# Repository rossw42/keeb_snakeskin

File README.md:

# Keyboard Snakeskin

Automatically generate a 3D printable case and magnetic carrycase for your custom split keyboard PCBs, from just the
outline. Also generates cases for other PCBs.

This case design generally uses a friction fit to get the PCB to stay in the
case. You can use hot glue instead if your printer tolerances are bad or
you want a sturdier/more permanent fit.
Cases have a removal cutout in one part of the wall for you to pull the case out
after pushing it in.

Inspired by and in collaboration with the [Compression keyboard](https://github.com/compressionKeyboards/compression4c) by Bennett Hermanoff. ([More images here](https://compressionkeyboards.com/)).

|  | |
| ------------- | -------------- |
|  *Example case rendered from the [maizeless](https://github.com/BlueDrink9/maizeless) PCB, with honeycomb base.* |  *Example [ferris](https://github.com/pierrechevalier83/ferris) case* |
|  *Corne* |  *Lily58 with a fat honeycomb* |
| *Carrycase with one case inside*. The carrycase is mirrored around the center, to allow for two halves of a split board to be carried together.  | Just the carrycase  |
| With tenting legs and strap loop  | One leg open  |

## Features

* Gives you a protective case for your keyboard PCBs, even if you aren't using
a popular design.
* Compact magnetic carrycase gives you ultimate portability, quick to unclip
and start typing (no faffing with bags or zips).
* Quick-tenting mechanism with quick-unfold leg(s), customisable for multiple angles and heights.
* Optional honeycomb base, to look great, save on weight and plastic, and show
off your custom PCB and top-notch (😉) soldering.
* Loop for strap attachment
    * Attach the boards to your legs for a standing setup,
    * Tie to a chair arm for a more ergonomic sitting setup,
    * use as a handle or tie to your bag.
* Works with both split and non-split board PCBs
* Works with any PCB of unusual shape, even non-keyboard PCBs for whatever random project you want an enclosure for.
* If you don't care about the magnets, you can input an SVG outline of a board with an existing case (e.g. commercial Ergodox or Voyager) and just print a carrycase for protecting the keys.
* Outputs as `STL` or `STEP`, so you can use this as the base shape for your own more exciting custom case designs (as long as they are provided under the same licence).

### Future feature ideas

* Unibody case generator, with customisable distances and angles. Possibly even
a temporary one (sit/clip your regular case into it to make it a unibody board
for the couch, then lift them up and use them separately at your desk).
* Integrate features with the carrycase. Possibly allow clipping the board
edges into the carrycase for a unibody angle, or clip the board onto the top as
a tenting mechanism.
* Strap loop on carrycase as a handle or to attach to a bag.
* Wrist wrest that magnetically snap to the case.
* Folding hinge join between the two halves, similar to the [Leaf fold](https://www.reddit.com/r/ErgoMechKeyboards/comments/1g9hv4a/introducing_leaf_fold_an_ultra_portable_keyboard/)
* Insets/holes under case to sit rubber feet in. (You can still use them currently, but they stick out of the bottom and may not be as stable.) This feature would probably be configured with a list of angles to place the holes at around the case edge (as well as hole diameter and depth, and maybe distance from the case edge). Subtracting holes from the final case would be quite easy to do manually from the .step output, so if you need this feature, you can probably do it yourself.
* Standoffs to screw in PCB --- I'm not likely to do this (at least certainly not automatically generating them from the PCB holes). This would be easy to add yourself from the .step output in another program like freecad, if you really need these.
* Different patterns for the bottom (like the popular organic void patterns).
* Position eyelets for slower but more flexibly screw-based tenting legs (like often seen in nyquist cases).

> See anything you like? Open an issue and express interest

**Tip**: Take note of the version of snakeskin you use to build your cases, as
well as your current config.
You may want to print new parts as features are released, and you'll want the
same config and major version to ensure the case is compatible.
Features may also get added that change case designs, and you'll want to know
that if you want to reprint parts that you already have.

## Usage

Overall:
1. In KiCad, export **just the edge cuts layer** as an SVG.
2. Customise the design parameters for your board, either by creating/modifying a config json, or passing arguments. At minimum I would suggest tweaking the cutout and magnet positioning for your board, although I suggest verifying the program runs without errors on your SVG with defaults before tweaking too many parameters.
3. Run `snakeskin.py --config path/to/config.json path/to/edge_cuts.svg`.
4. (Optional) Read the [Configuration](#configuration) section to tweak for your board.

Note: this is still a young project, so please feel free to open issues. Include the SVG and config you are having issues with.

### Install

`pip install --user keeb-snakeskin` installs this package and dependencies, and
should create a new executable `snakeskin` in your python scripts folder.

Use `pip install --user git+https://github.com/BlueDrink9/keeb_snakeskin.git` for the latest git version.

#### Windows Installation

If you're on Windows with Python 3.14+, you may encounter compatibility issues since `build123d` and its dependencies don't yet support the latest Python versions. Here's how to resolve it:

1. **Use Python 3.13** (recommended):
   ```powershell
   # Check available Python versions
   py -0
   
   # Install with Python 3.13
   py -3.13 -m pip install --user keeb-snakeskin
   ```

2. **Run snakeskin with Python 3.13**:
   ```powershell
   py -3.13 -m keeb_snakeskin.snakeskin --output_dir my_case path/to/edge_cuts.svg
   ```

If you're installing from source on Windows:
```powershell
# Clone the repository
git clone https://github.com/BlueDrink9/keeb_snakeskin.git
cd keeb_snakeskin

# Install in development mode with Python 3.13
py -3.13 -m pip install -e .

# Run with Python 3.13
py -3.13 -m keeb_snakeskin.snakeskin --output_dir my_case preset_outlines/ferris.svg
```

### Input File

The program requires an SVG outline of the PCB, which is then used as the base shape for the case.
You can pass in either a:
* `.svg` file
* `kicad_pcb` file (if `kicad-cli` is installed and on your `$PATH`)

If KiCad cannot be found, you will have to convert your file to svg manually.

Example usage:
```bash
snakeskin -o maizeless ~/src/maizeless/pcb/build/maizeless.svg --split false
```

The `-o` option specifies the output directory for your case files. If it is
not an absolute path, it will be created as a subfolder or file within the
`build` folder.

In this case the output would be `./build/maizeless/case.step` and `./build/maizeless/case_mirrored.stl`

`--split false` sets a configuration option. See the [Configuration](#configuration) section for more information on how to customise the case design.

#### Getting the starting svg

Clean and working outline svgs for some boards are already included in the `./preset_outlines/` folder.
Currently this includes:
* [ferris (0.1)](https://github.com/pierrechevalier83/ferris)
* [maizeless](https://github.com/BlueDrink9/maizeless)
* [corne](https://github.com/foostan/crkbd) (cherry version, not sure what compatibility is like with other versions - it depends purely on the PCB outline)
* [Sofle](https://github.com/josefadamcik/SofleKeyboard) (v1 --- v2 works directly from the `.kicad_pcb`)

In kicad, export just the edge.cuts layer as plot format `svg` (board only, not page).
Note that KiCad has two ways to do this - plotting fabrication as an SVG, and exporting just edge as an SVG directly. The latter gives a more stable output.
Ensure coordinate output is mm if relevant, and all the 'plot' general options are unchecked.

You can do this with the cli via
`kicad-cli pcb export svg  --exclude-drawing-sheet --drill-shape-opt 1 --layers Edge.Cuts --output build/outline.svg ~/src/maizeless/pcb/maizeless.kicad_pcb`.
If you have kicad-cli on your `$PATH`, you can directly pass the `.kicad_pcb`
file to `snakeskin.py` and this export will be done for you.

If you only have a [keyboard-layout-editor](https://keyboard-layout-editor.com/) file, you can
generate an input SVG or KiCad PCB first with tools like
* https://github.com/fcoury/kbpcb
* https://kb.xyz.is/
* https://github.com/adamws/keyboard-tools

#### Troublesome PCBs/input files

This program requires the PCB outline to be a single, closed path. Complicated
PCBs will not work out of the box, for example ones with:

* large irregular holes (e.g. LED holes; vias and holes for keyboard switches are fine)
* internal cutouts (like for mid-mount connectors),
* breakable/mouse nibble columns,
* multiple halves
* multiple halves in a PCB frame

That being said, you can still use this program; you'll just need to manually
edit the SVG outline. Usually this will be as simple as removing the second
half or any internal holes. If you do this for a popular board, please open a PR to
share the resulting SVG (and ideally config json) in `./preset_outlines/`

**Note**: SVG outlines must not contain borders or technical drawings, as are
often exported by default in KiCad. Remove these if you are using an SVG input.

##### Troubleshooting steps to try
* First check with default settings
* Remove any internal holes or cutouts from the SVG
* Set `tiny_edge_rounding` to `True` in your config
* In Inkscape, select the outline, then `Path -> Stroke to Path`, then `Path -> Union`
* In Inkscape, select the outline, then `Path -> Simplify`
* In Inkscape, edit path nodes and ensure they are all connected (small
disconnections should be handled by the code, but large ones, especially in PCBs with bezier edges, may cause issues). To connect them, go to node edit mode, and draw a box around each node and each close pairs of nodes (drawing a box is important, don't just click) to select them both, then double-click `Join selected nodes` in the node editing toolbar.
* Note that KiCad usually exports a double layer for the edge cuts, so you may
  need to delete one before simplifying.

#### Other PCB file formats
##### DXF

These are easily converted to SVG in Inkscape or other tools, so Snakeskin doesn't support them directly.
The inkscape command line will not export them correctly; the GUI must be used.
Open the DXF, then save as an SVG. Do not export as SVG, this may change the
shape.

##### Gerber

Only use this format if you can't get an outline some other way. The steps below should be unnecessary if you can get an SVG or KiCad PCB.

Edge cut exports in gerber format (i.e. `.gm1` or `.gbr`) don't output an
outline, rather they output a thin shape surrounding the board that *looks*
like an outline. You will need to modify this, e.g. in Inkscape, to get a
single outline path. For convenience, passing the `.gm1` file to `snakeskin`
will output an SVG of the edge cuts in the build folder, which you can then
modify and pass back in. (Requires the `pygerber` pip package to be installed.)

To fix this in Inkscape, you can:
1. Select all, then Path -> Stroke to Path (ctrl + alt + c)
2. Edit -> Find and replace to search and select all paths with "circle" in their id, then delete them.
3. Go to preferences (Edit -> Preferences -> imported images) and set the "Resolution for create bitmap copy" to 1000 dpi.
4. Select the paths, then Edit -> Make a bitmap copy.
5. Select the bitmap copy, go to Path -> Trace bitmap, select detection mode to "centerline tracing (autotrace)".
6. Ensure the path is closed (if there are gaps, you can use the node editing tool to connect the ends of the path).
7. Compare the result against the original paths, and tweak nodes to get it as close as possible.
8. Delete any other paths and objects under the view -> layers and objects panel, to ensure only the outline is left.

### Printing

Designed for PLA, but I've had suggestions that TPU will create a great softer,
more skinlike case. If you have access to it, I would suggest trying that - at
least for the inner case, if not the legs and carrycase.

#### Supports
These designs are designed to be printed in PLA without supports where possible. There
is only two severe (90 degree) overhang in the design, which is the first
blocker of the carrycase and the first carrycase finger cutout.
These should be the only parts that needs supports with the default featureset.
Setting your printer to only print overhangs over 70 degrees should be enough
to automatically support only these parts.

If you aren't printing the carrycase, you shouldn't need supports at all.
If you are using advanced features like the strap loop, you may need additional supports.
If `flush_carrycase_lip` is `False`, you will need short supports all around the bottom of the
carrycase, and its top lip. Again, setting overhangs to 70 degrees should
allocate supports appropriately.

### Assembly

For the basic case, just insert the PCB with a bit of force to get the friction
fit. You may choose to add hot clue underneath for a more permanent fit.

#### Carrycase

The only additional assembly required is inserting magnets. Check out [the Compression
video](https://www.youtube.com/watch?v=eRLCBHWX4eQ&t=905s) to get the general idea.
Only the carrycase magnets should need glue, the case magnets should be held in
by the PCB.

The magnets can be tricky to insert, because you need the orientation lined up between the case and carrycase, and if adjacent magnets are close together, they will interfere with the alignment during placement.
The easiest way to insert the magnets is to do the carrycase first, gluing the magnets that are far away from each other first, letting them dry, then doing the magnet locations adjacent to them.
Then, insert the cases into the carrycase one at a time and insert the magnets, letting the glued carrycase magnets orient the case magnets for you.

#### Tenting legs
1. Align the leg hinges with the case hinges (there should only be one sensible way they fit) and insert the nut.
Screw the bolt in.
2. Add a small piece of velcro to the top of the smallest leg. Add the other
   piece, then press the leg up into the case. Ideally the second piece should then glue to the
PCB. The velcro holds it in place. Feel free to come up with other mechanisms
for keeping it in place, but velcro is an easy solution that doesn't require
much force to remove. I got my velcro from an old bike helmet.

### Visual configurator (browser)

If editing JSON by hand sounds painful, there's a local HTML configurator that
renders your PCB outline and lets you drag the cutout/magnet/lip positions
around the case wall, then download the resulting `config.json`.

It runs entirely in the browser, with no build step or server configuration needed.

#### Launching the Configurator

**Linux/Mac:**
```sh
cd path/to/keeb_snakeskin
make configurator
# or manually:
python -m http.server 8771
```

Then open http://localhost:8771/configurator/ in your browser.

**Windows:**
```powershell
cd path\to\keeb_snakeskin
python -m http.server 8771
```

Then open http://localhost:8771/configurator/ in your browser.

#### Using the Configurator

1. **Load a PCB outline** — Click "Load SVG" and select your edge cuts file, or pick a preset outline
2. **Load a config (optional)** — Click "Load config JSON" to start from an existing config, or pick a preset
3. **Adjust parameters** — Edit the form fields on the right, or drag handles on the canvas:
   - Drag the **cutout handle** to reposition the removal cutout
   - Drag **magnet/lip handles** if using a carrycase
   - Drag **additional cutout handles** for TRRS cables or other features
4. **Download your config** — Click "Download config.json" and enter a name
5. **Generate your case** — Use the downloaded config with snakeskin

#### Generating Cases from Downloaded Config

Once you've downloaded `config.json` from the configurator:

Linux/Mac:
```sh
snakeskin -c config.json -o my-board path/to/edge_cuts.svg
```

Windows with Python 3.13:
```powershell
py -3.13 -m keeb_snakeskin.snakeskin -c config.json --output_dir my-board path/to/edge_cuts.svg
```

The downloaded JSON contains only fields that differ from the defaults, so
upgrading snakeskin won't drag stale values along.

### Configuration

Other than the case design parameters below, you can also input the following
arguments:
- `-o`, `--output`: Output directory or file path (default: "build")
- `-c`, `--config`: Path to the JSON configuration file

The following tables describe the possible variables you can specify for
your case creation.
To modify the paramters, pass a path to a `.json` file with
`-c path/to/cfg.json`, and/or pass individual parameters as command line arguments.
See `python snakeskin.py --help` for more information and for defaults.
The json should have anything you want to override from
defaults specified as a top level key:value. See `./preset_configs/` for
examples.
Using both the json and command line argument for a parameter will take the
command line argument as priority.

You may prefer to modify an existing config, from `./preset_configs/`.
Currently there are configs for:
* [ferris](https://github.com/pierrechevalier83/ferris)
* [maizeless](https://github.com/BlueDrink9/maizeless)
* [corne](https://github.com/foostan/crkbd) (cherry version, although it may not have enough height in the carrycase for cherry keycaps - measure and tweak yourself!)
* [Sofle (v1 and v2)](https://github.com/josefadamcik/SofleKeyboard)
* [Lily58](https://github.com/kata0510/Lily58)

Please note that these configs are on a best-effort basis only, and so far only
the Maizeless has been tested on a real print.

| Parameter name | Example value + unit| Description |
| -------------- | ------------- | ----------- |
| `split`| True | If True, generate mirrored pair of files for a split board |
| `carrycase` | True | Whether the output designs should incorporate the compression-style carrycase. Will affect the main case as well. |
| `honeycomb_base` | True | Make the base of the case a honeycombed/hexagon cage instead of solid |
| `flush_carrycase_lip` | True | Two options for holding the pcb case into the carrycase: a lip that extends into the carrycase center, with a matching cutout in the pcb case; or, a lip that sits a bit above and below the carrycase. If false, the pcb case will have a flat bottom and your tolerances between the case and carrycase can be tighter, giving a better fit when in the case. However, it will require more supports when printing. |
| `strap_loop` | False | Adds a loop on the left most end of the boards for a strap, e.g. for mounting on legs or chair arms. Experimental. If you want something on the other side, also include the tenting flap hinge and use the bolt. |
| `tenting_stand` | False | Use the special quick-deploy tenting mechanism. This parameter adds the hinge to the case (and a gap for it in the carrycase) and exports the requested tenting flaps to the output directory. This creates a hinge at the end of the case, which is designed for a hex nut and countersunk bolt of customisable length. |
| `output_filetype` | `.step` | `.step` or `.stl`. What filetype the case will be exported as. |
| `tiny_edge_rounding` | False | Try enabling this if your case is erroring out with an OCP error, or other invalid shape error. Small hack to work around engine bugs when your outline has tiny edges that may cause problems during offset or extrude operations. May also make things worse, and will very slightly round off internal corners (which shouldn't prevent the PCB from fitting) |
| `simplify_beziers` | False | Try enabling this if your case is erroring out with an OCP error, or other invalid shape error. In some PCB outlines where rounded edges are defined using beziers (e.g. the corne), the 3D engine fails at offsetting or tapering the edges. This option converts beziers to straight line approximations. The approximation is crude, so you may get more accurate results if you do this yourself in inkscape with Extensions > modify path > Approximate curves by straight lines. This setting will probably cut corners a little, making the fit of the case around the PCB a bit tighter. Either increase the tolerance (if you have a lot of corners) or just carve out any tight bits after printing. |
| `base_z_thickness` | 3 mm | Z thickness of bottom of the case, in mm |
| `wall_xy_thickness` | 3 mm | Thickness/width in X and Y of the wall around the edge of the PCB, holding it in the case.  Top and bottom wall tolerance will also affect the thickness that actually gets printed. Recommend 2 + `magnet_separation_distance` if you're using the carrycase, so the magnets don't rattle. If it's larger, you'll have to glue the magnets into the case as well as the carrycase. If you are using the carrycase and have tall keys (i.e. not flat-soldered chocs) close to the edge of the PCB, you may need to make this bigger and tweak the carrycase lip to ensure enough clearance of the carrycase blocker when you insert the board. |
| `wall_z_height` | 4.0 mm | Z height of the wall **from the bottom of the PCB** (total case wall height will include z_space_under_pcb). The default includes room for magnets for the carrycase. If you aren't adding a carrycase, 1.6 is a good height for a standard PCB thickness if you just want to cover the pcb. |
| `z_space_under_pcb` | 1 mm | The size of the gap beneath the PCB, to leave room for through-hole pins, wires, hotswap sockets etc on the underside. Modify this to at least 1.85 if you are using kailh hotswap sockets under the PCB, for example. Also increase it if you want to have bigger tolerences for the fit and need more space for the walls to narrow in. By default, leaves just enough space for the pins of a choc switch directly soldered into a 1.6 mm pcb (which I measure stick out at about 0.83 mm). |
| `wall_xy_bottom_tolerance` | -0.3 mm | Amount of space between the PCB and the case walls near the case bottom, where PCB should sit (i.e. above z_space_under_pcb). Intended as a -ve value to get a tight friction fit. This is implemented with a scaling hack because of engine limitations, so I'd encourage measuring the result in a CAD program if you need it exact. |
| `wall_xy_top_tolerance` | 0.3 mm | Amount of space between the widest part of the walls (at the top) and the PCB outline. Adjust this depending on printer tolerances and how tight you want the friction fit. You may want to increase `z_space_under_pcb` if the difference between this and `wall_xy_bottom_tolerance` is large |
| `chamfer_len` | 1 mm | Chamfer length on the case edges. |
| `cutout_position` | 10 | Location along the walls of the pcb case for a cutout to remove the PCB from the board, as an angle from the center of the case. Angle is between -180 and 180, with 0 pointing in +ve X axis, and -90 pointing in the -ve Y axis. Not every angle is possible, so your argument will be mapped to the closest acceptable angle. I suggest this position also be the location of your USB connector. |
| `cutout_width` | 15 mm | Width of the removal cutout. May cut out more if the area isn't a straight line. |
| `additional_cutouts` | `[[10, 15]]` | List of extra cutouts in the wall to add, in the format `[[angle at center of cutout, width],]`. See `cutout_position` for info about the angles. Use this to place an extra cutout for your TRRS cable, if it's a wired board. |
| `honeycomb_radius` | 6 mm | Radius of the blank space hexagons for the honeycomb case base (major/inscribed radius) |
| `honeycomb_thickness` | 2 mm | Thickness of the bars (space between hexagons) of the honeycomb case base |
| `strap_loop_thickness` | 4 mm | Thickness (in XY) of the strap loop |
| `strap_loop_end_offset` | 0 mm | Inset from the ends of the case where the strap starts. Fiddle with this to avoid or merge with corners, for example. |
| `strap_loop_gap` | 5 mm | Gap left in the strap loop for the strap to go through. |
| `tent_legs` | `[[30, 50, 0], [20, 30, 15]]`, | List of tent legs as `width` (Y len), `length` (X len) and `tenting_angle` (slope of the tip), which will be exported as separate files, as well as cut out of the keyboard base. Multiple legs will be nested within each other (to the extent possible with the length of the hinge). Width is the width of the leg flap at the end furthest from the hinge. The tenting angle is the angle from 0 that the keyboard will be rotated clockwise when looking in the direction of the X axis (i.e. angle it will tilt the board face towards/away from the user). The end widths must decrease with length, or nesting will fail. |
| `tent_hinge_position_offset` | 0 | Amount up or down to reposition the hinge. By default (0) it's the center of the board bounding box. |
| `tent_hinge_width` | 5 | How thick in the Y axis the hinges are that hold the tenting flaps. Keep this short if you have lots of tenting flaps, otherwise you may as well increase it to increase the strength. |
| `tent_hinge_bolt_d` | 3 (mm, == M3) | Bolt diameter specification for the tenting stand hinge. If you are using imperial bolts, be sure to convert the official size to mm, don't measure the thread. Keep this as small as you can, because the bigger the hole, the less plastic holding it in place. |
| `tent_hinge_bolt_l` | 60 mm | Length of bolt for the tenting stand hinge, including head assuming it's countersunk. I'd suggest getting something as big as you can find for the size of your case. Push rods might help getting something really long, with small diameters (but will need two nuts). |
| `tent_hinge_bolt_head_d` | 6.94 mm | Diameter of bolt head (only used for countersink). |
| `tent_hinge_nut_l` | 5.5 mm | Length of nut retention hole |
| `tent_hinge_nut_d` | 2.4 mm | Inscribed diameter of nut for tent hinge bolt |

#### Carrycase options

If you are creating a carrycase (`"carrycase": true`), the following additional parameters are available in the same configuration:

| Parameter name | default value | description |
| -------------- | ------------- | ----------- |
| `carrycase_tolerance_xy` | 0.8 mm | Gap size between the pcb case and the carry case. May need playing around with on your printer to get a good fit. Err on the side of too large if you don't want to print too much. |
| `carrycase_tolerance_z` | 0.5 mm | Gap size between the pcb case and the carry case blockers. May need playing around with on your printer to get a good fit. Larger carrycase tolerances will make it easier to get the case into and out of the carrycase, at the cost of tightness of fit once it's in there. |
| `carrycase_wall_xy_thickness` | 2 mm | Thickness of the carrycase outer wall |
| `carrycase_z_gap_between_cases` | 8 mm | How much room to leave between each pcb (well, actually between the tops of the pcb case walls). By default this works for soldered in choc v1 switches with thin keycaps (and it will leave about 1 mm between them when they are in the case. An easy way to calculate it is to measure the distance from the bottom of the PCB to the highest part of your keycaps, subtract `wall_z_height`, and add 1. |
| `carrycase_cutout_position` | -90 | Location  along the walls of the carrycase for the cutout that lets you remove the cases, as an angle from the center of the case. Should be opposite the lip, on the same side as the magnets. See `cutout_position` for info about the angles. |
| `carrycase_cutout_xy_width` | 15 mm | Width of the finger cutout for removing the boards from the case. May cut out more if the area isn't a straight line. |
| `lip_len` | 1.5 mm | Length of the lip (not including carrycase tolerance, i.e. this is the xy length that protrudes over the case). |
| `lip_position_angles` | [160, 30] | A list of two angles, [start_angle, end_angle], that defines the position of the lip on the case. Measured in degrees from the positive X-axis. Positive angles are measured counterclockwise, with 0 degrees being the positive X-axis and 90 degrees being the positive Y-axis, -90 is the direction of the negative Y axis.The difference between the start and end angles must be less than 180 degrees. It is recommended to set the angles to cover a long, straight section of the case. This must be opposite to the location of the finger cutout on the carry case and the magnets. |
| `magnet_position` | -90 | Location  along the walls of the carrycase and case where the magnets will be centered, as an angle from the center of the case. Angle is between -180 and 180, with 0 pointing in +ve X axis, and -90 pointing in the -ve Y axis. |
| `magnet_separation_distance` | 0.3 mm | Amount of plastic separating the magnets in the case from the magnets in the carrycase. How thick the case wall |
| `magnet_spacing` | 12 mm | Distance between the centers of magnets along the same wall of the case |
| `magnet_count` | 8 | Number of magnets per case (a split board and compression case will need 4× this amount to complete the build). The carrycase finger cutout may remove a couple of these, so check the output. I find 5 is just enough for a stable hold on my 42-key board, but you may as well print a few more and glue just as many as you need. |

## Development

Versioning will follow [semantic versioning](https://semver.org/) to an extent.
Features will be added in minor versions, and bugfixes in patch versions.
Designs will be considered "breaking" changes if a plain case printed with a
prior version would no longer fit the carrycase/other features added in a new
version. This does not apply to more advanced features.

## Final notes

This took a _lot_ of time and brainpower to work through. My sincerest hope is
that it is useful, and unlocks the ability to have cool, super-portable cases
for your keyboards. I want people to feel that they can create a keyboard that
fits their hands without forfeiting access to cool cases, rather than having to
go with a more popular form factor.

If you found it useful, indicating your appreciation will fill me with joy. A
star or a share are fantastic, letting me know someone has found this useful
(or even just cool). Even better, you might choose to donate a token of
appreciation, either via Github or crypto:
* bitcoincash:qp9c4ppt24c2ewzypv0pk0euapcyr92n85y7rhes7v
* monero: 48x8HBjE5zeHyk73wtkKdZUJLgBnRFQKWjTnawRFqu3Z5Ldd3CMEGWLE4v1UV1vqSAZCYJRWnDX97iJwxeDtkT9W489vYWr

I'd also like to encourage you to sponsor
[build123d](https://github.com/gumyr/build123d), the technology behind this
project. Their Discord was a great help in figuring out many of the
representational challenges.

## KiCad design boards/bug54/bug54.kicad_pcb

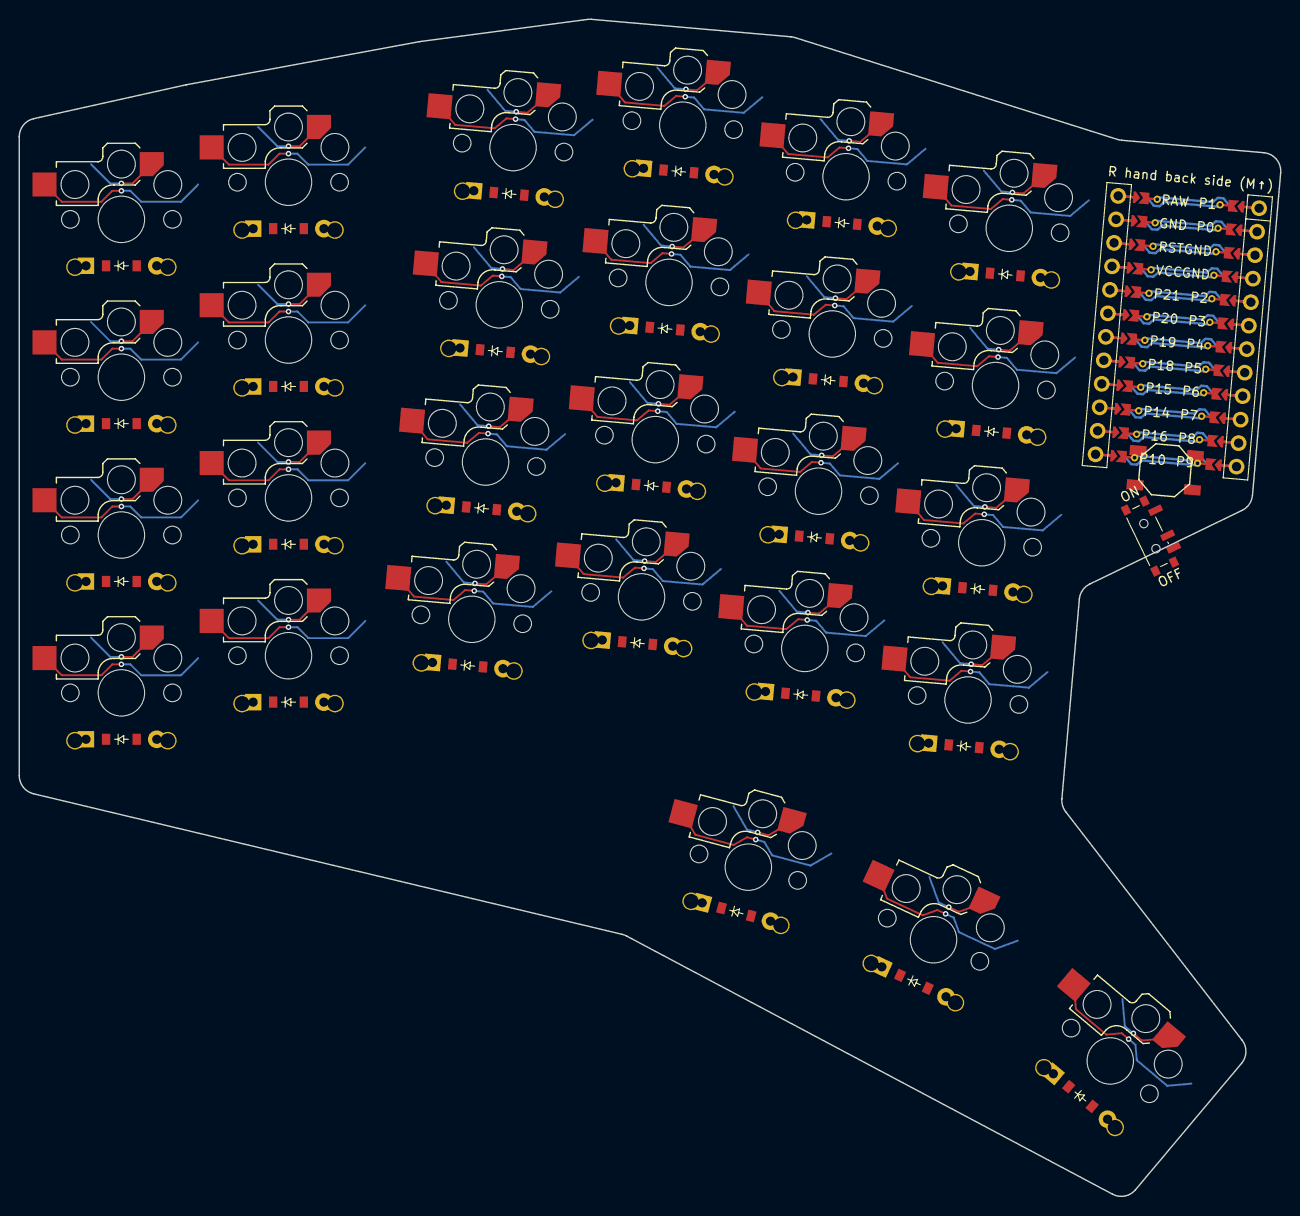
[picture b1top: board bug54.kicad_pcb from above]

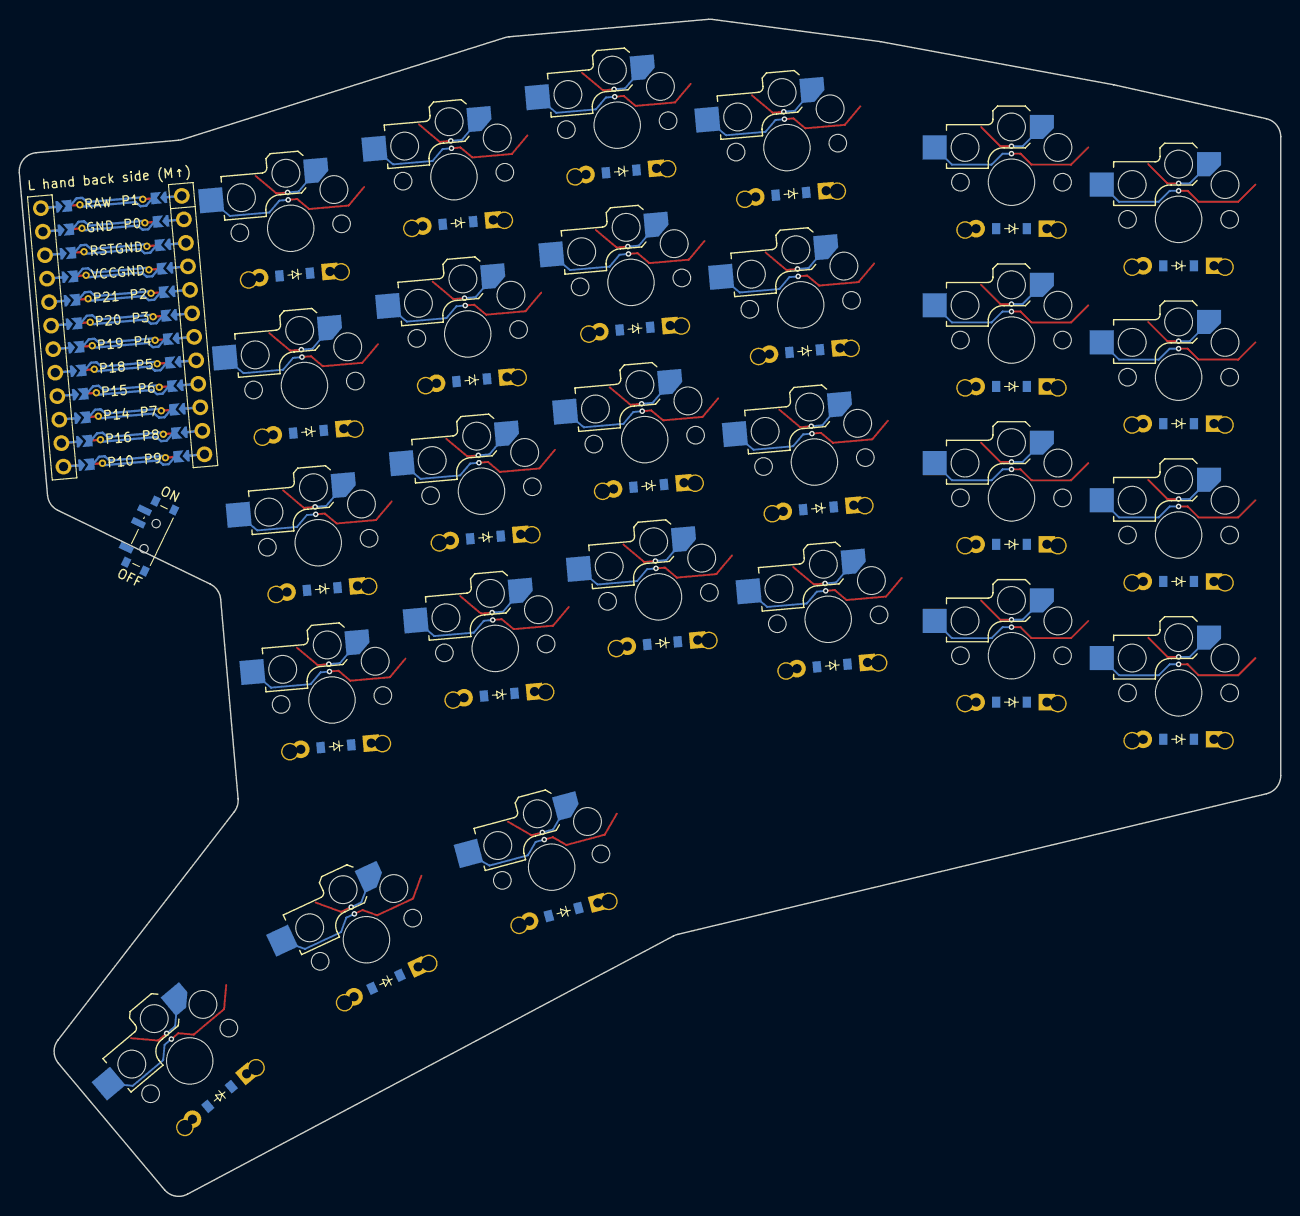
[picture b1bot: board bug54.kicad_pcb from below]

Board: 2 copper layers, 135.9 x 126.8 mm, 57 parts (27 on the bottom side), 42 nets.

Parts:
B1: SW_TACT_ALPS_SKQGABE010
D1, D2, D3, D4, D5, D6, D7, D8, D9, D10, D11, D12, D13, D14, D15, D16, D17, D18, D19, D20, D21, D22, D23, D24, D25, D26, D27: ComboDiode
MCU1: mcu_nice_nano
PWR1: power_switch_smd_side
S1, S2, S3, S4, S5, S6, S7, S8, S9, S10, S11, S12, S13, S14, S15, S16, S17, S18, S19, S20, S21, S22, S23, S24, S25, S26, S27: switch_choc_v1_v2

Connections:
BAT_P: PWR1.1, PWR1.3
GND: B1.1, MCU1.103, MCU1.104, MCU1.123
P7: D25.1, D26.1, D27.1, MCU1.110
P8: D2.1, D6.1, D10.1, D14.1, D18.1, D22.1, MCU1.111
P9: D1.1, D5.1, D9.1, D13.1, D17.1, D21.1, MCU1.112
P10: D3.1, D7.1, D11.1, D15.1, D19.1, D23.1, MCU1.113
P14: MCU1.115, S17.1, S18.1, S19.1, S20.1, S26.1
P15: MCU1.116, S13.1, S14.1, S15.1, S16.1, S25.1
P16: MCU1.114, S21.1, S22.1, S23.1, S24.1, S27.1
P18: MCU1.117, S9.1, S10.1, S11.1, S12.1
P19: MCU1.118, S5.1, S6.1, S7.1, S8.1
P20: MCU1.119, S1.1, S2.1, S3.1, S4.1
P21: D4.1, D8.1, D12.1, D16.1, D20.1, D24.1, MCU1.120
RAW: MCU1.124, PWR1.2
RST: B1.2, MCU1.122
far_bottom: D1.2, S1.2
far_home: D2.2, S2.2
far_secondary: D3.2, S3.2
far_top: D4.2, S4.2
index_bottom: D17.2, S17.2
index_home: D18.2, S18.2
index_secondary: D19.2, S19.2
index_top: D20.2, S20.2
inner_bottom: D21.2, S21.2
inner_home: D22.2, S22.2
inner_secondary: D23.2, S23.2
inner_thumb: D25.2, S25.2
inner_top: D24.2, S24.2
middle_bottom: D13.2, S13.2
middle_home: D14.2, S14.2
middle_secondary: D15.2, S15.2
middle_thumb: D26.2, S26.2
middle_top: D16.2, S16.2
outer_thumb: D27.2, S27.2
pinky_bottom: D5.2, S5.2
pinky_home: D6.2, S6.2
pinky_secondary: D7.2, S7.2
pinky_top: D8.2, S8.2
ring_bottom: D9.2, S9.2
ring_home: D10.2, S10.2
ring_secondary: D11.2, S11.2
ring_top: D12.2, S12.2

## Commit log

2026-05-25 first commit of my fork
2026-05-25 moving some files around
2026-06-07 Add Windows support, fix output directory handling, and add om board example
    - Update pyproject.toml to support Python 3.14+ and relax build123d version constraints
    - Update README with Windows installation instructions using Python 3.13
    - Fix output_dir to respect explicit user paths instead of always prepending build/
    - Add boards/om/ example with config and generated case files
    - Update configurator version for cache refresh
2026-06-07 Fix unibody output filenames to match config mode
    - unibody_mode=tray generates unibody_tray.stl
    - unibody_mode=case generates unibody_case.stl
    - Output filenames now clearly correspond to their configuration
2026-06-07 Revert to tray-only unibody support, update om config
    - Keep unibody_tray output for now (case mode is future work)
    - Update om.json to use unibody_mode: tray
    - Output filenames correctly match config: unibody_tray.stl when tray mode is active
2026-06-07 Expand configurator documentation with detailed launch and usage instructions
